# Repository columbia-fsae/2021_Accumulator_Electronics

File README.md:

View this project on [CADLAB.io](https://cadlab.io/project/23124). 

# 2021_Accumulator_Electronics

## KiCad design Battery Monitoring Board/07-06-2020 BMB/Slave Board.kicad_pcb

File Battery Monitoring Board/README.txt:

Include the following libraries from KiCAD Libraries folder:

SYMBOL LIBRARIES:

1) arduino_shieldsNCL
2) LTC6820IMS#PBF
3) LTC6804-2
4) arduino_micro_shield

FOOTPRINT LIBRARIES:

1) arduino_shields
2) Arduino
3) LTC6804-2
4) LTC6820IMS#PBF
5) Arduino_Shield_Modules_for_KiCad_V3

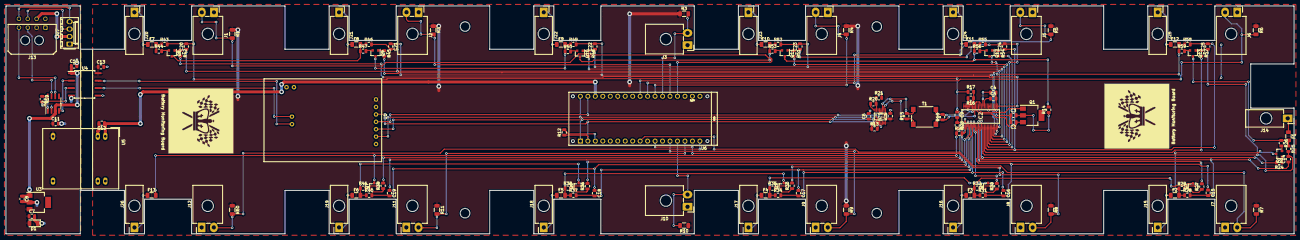
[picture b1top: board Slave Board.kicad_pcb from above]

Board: 2 copper layers, 438.0 x 77.5 mm, 148 parts (0 on the bottom side), 122 nets.

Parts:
C1, C3, C6, C7, C8, C9, C10, C11, C12, C13: 100n; C_0805_2012Metric
C2, C4, C5: 1u; C_0805_2012Metric
C14, C15, C16, C17, C18, C19, C20, C21, C22, C23, C24, C25: 10n; C_0805_2012Metric
D1: DIODE; D_1206_3216Metric
F1, F2, F3, F4, F5, F6, F7, F8, F9, F10, F11, F12, F13: Fuse; Fuse_1206_3216Metric
IC1: LTC6820IMS#PBF; SOP50P490X110-16N
IC2: LTC6804-2; SOP50P780X200-48N
J1, J2, J3, J4, J5, J6, J7, J8, J9, J10, J11, J12: Conn_01x02; TE_MATE-N-LOK_1-770966-x_1x02_P4.14mm_Horizontal
J13: Conn_01x08; Molex_Micro-Fit_3.0_43045-0800_2x04_P3.00mm_Horizontal
J14, J15, J16, J17, J18, J19, J20, J21, J22, J23, J24, J25, J26: Conn_01x01; TE_MATE-N-LOK_1-794374-x_1x01_P4.14mm_Horizontal
J27: Conn_01x04; Molex_KK-254_AE-6410-04A_1x04_P2.54mm_Vertical
Q1: Q_NPN_BCE; SOT-223
Q2, Q3, Q4, Q5, Q6, Q7, Q8, Q9, Q10, Q11, Q12, Q13: Q_PMOS_GSD; SOT-23
R1, R2, R3, R4, R5, R6, R7, R8, R9, R10, R11, R60: 680; R_1206_3216Metric
R12: NC; R_0805_2012Metric
R13: 5k; R_0805_2012Metric
R14, R15, R18, R22, R23, R25, R28, R31, R34, R37, R40, R43, R46, R49, R52, R55, R58: 100; R_0805_2012Metric
R16, R20: 1k21; R_0805_2012Metric
R17, R21: 860; R_0805_2012Metric
R19: 10k; R_0805_2012Metric
R24, R27, R30, R33, R36, R39, R42, R45, R48, R51, R54, R57: 3k3; R_0805_2012Metric
R26, R29, R32, R35, R38, R41, R44, R47, R50, R53, R56, R59: 33; R_0805_2012Metric
T1: PE-68386NL; Pulse_PA2001NL
U1: MCP2551_CANmodule; MCP2515_ArduinoShield
U2: MCP2551-I-SN; SOIC-8_3.9x4.9mm_P1.27mm
U3: OKI-78SR-3.3_1.5-W36-C; SOT-223
U4: ISO1050DUB; SOP-8_6.62x9.15mm_P2.54mm
U5: TMR_1-1212; Converter_DCDC_TRACO_POWER_TEL_10-xxxx_THT
U6: ARDUINO_MICRO_SHIELD; Arduino_Micro_Socket

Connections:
+5V: C1.1, C6.1, C13.1, IC1.1, IC1.6, IC1.7, IC1.8, IC1.9, IC1.12, R1.1, R2.1, R3.1, R4.1, R5.1, R6.1, R7.1, R8.1, R9.1, R10.1, R11.1, R13.1, R60.1, U1.7, U4.8, U6.5V
+12V: C7.1, C11.1, D1.2, J13.2, U3.3, U5.2
C0: C2.2, C3.1, C4.2, C5.2, C9.1, C20.2, IC2.26, IC2.30, IC2.31, IC2.45, IC2.46, IC2.47, IC2.48, R17.1, R43.2
C1: C20.1, C21.2, IC2.24, R46.2
C2: C21.1, C22.2, IC2.22, R49.2
C3: C22.1, C23.2, IC2.20, R52.2
C4: C23.1, C24.2, IC2.18, R55.2
C5: C24.1, C25.2, IC2.16, R58.2
C6: C14.2, C25.1, IC2.14, R25.2
C7: C14.1, C15.2, IC2.12, R28.2
C8: C15.1, C16.2, IC2.10, R31.2
C9: C16.1, C17.2, IC2.8, R34.2
C10: C17.1, C18.2, IC2.6, R37.2
C11: C18.1, C19.2, IC2.4, R40.2
C12: C19.1, IC2.2, R22.2
CANH: J13.3, U2.7
CANL: J13.4, U2.6
CS: IC1.5, R12.1, U1.5, U6.SS
Cell0: F7.2, R43.1, R44.1
Cell1: F8.2, Q8.3, R46.1, R47.1
Cell2: F9.2, Q9.3, R49.1, R50.1
Cell3: F10.2, Q10.3, R52.1, R53.1
Cell4: F11.2, Q11.3, R14.2, R55.1, R56.1
Cell5: F12.2, Q12.3, R58.1, R59.1
Cell6: F1.2, Q13.3, R25.1, R26.1
Cell7: F2.2, Q2.3, R28.1, R29.1
Cell8: F3.2, Q3.3, R31.1, R32.1
Cell9: F4.2, Q4.3, R34.1, R35.1
Cell10: F5.2, Q5.3, R37.1, R38.1
Cell11: F6.2, Q6.3, R40.1, R41.1
Cell12: F13.2, Q7.3, R22.1, R23.2
DCDC+: J13.6, J27.2
DRV: IC2.38, Q1.1
GND: C7.2, C8.2, C10.2, C11.2, D1.1, J13.1, J13.5, J27.1, R19.2, U2.2, U3.2, U4.4, U5.1
GND_ISO: C1.2, C6.2, C12.2, C13.2, IC1.13, IC1.14, J1.1, J2.1, J3.1, J4.1, J5.1, J6.1, J7.1, J8.1, J9.1, J10.1, J11.1, J12.1, R21.2, U1.6, U4.5, U5.6, U6.GND
IM: IC1.10, R15.1, T1.3
IMA: IC2.41, R18.1, T1.4
IP: IC1.11, R15.2, T1.1
IPA: IC2.42, R18.2, T1.6
ISO_CANH: U1.8, U4.7
ISO_CANL: U1.9, U4.6
unnamed: C3.2, Q1.2, R14.1
unnamed: C4.1, IC2.35
unnamed: C5.1, IC2.34
unnamed: C9.2, IC2.1, R23.1
unnamed: F1.1, J14.1
unnamed: F2.1, J15.1
unnamed: F3.1, J16.1
unnamed: F4.1, J17.1
unnamed: F5.1, J18.1
unnamed: F6.1, J19.1
unnamed: F7.1, J20.1
unnamed: F8.1, J21.1
unnamed: F9.1, J22.1
unnamed: F10.1, J23.1
unnamed: F11.1, J24.1
unnamed: F12.1, J25.1
unnamed: F13.1, J26.1
unnamed: IC1.15, R20.2, R21.1
unnamed: IC1.16, R20.1
unnamed: IC2.43, R16.1, R17.2
unnamed: IC2.44, R16.2
unnamed: Q2.1, R24.1
unnamed: Q2.2, R26.2
unnamed: Q3.1, R27.1
unnamed: Q3.2, R29.2
unnamed: Q4.1, R30.1
unnamed: Q4.2, R32.2
unnamed: Q5.1, R33.1
unnamed: Q5.2, R35.2
unnamed: Q6.1, R36.1
unnamed: Q6.2, R38.2
unnamed: Q7.1, R39.1
unnamed: Q7.2, R41.2
unnamed: Q8.1, R42.1
unnamed: Q8.2, R44.2
unnamed: Q9.1, R45.1
unnamed: Q9.2, R47.2
unnamed: Q10.1, R48.1
unnamed: Q10.2, R50.2
unnamed: Q11.1, R51.1
unnamed: Q11.2, R53.2
unnamed: Q12.1, R54.1
unnamed: Q12.2, R56.2
unnamed: Q13.1, R57.1
unnamed: Q13.2, R59.2
unnamed: R12.2, U6.TX
unnamed: R19.1, U2.8
PWM_Fans: J13.8, J27.4
RXD: U2.4, U4.2
S1: IC2.25, R42.2
S2: IC2.23, R45.2
S3: IC2.21, R48.2
S4: IC2.19, R51.2
S5: IC2.17, R54.2
S6: IC2.15, R57.2
S7: IC2.13, R24.2
S8: IC2.11, R27.2
S9: IC2.9, R30.2
S10: IC2.7, R33.2
S11: IC2.5, R36.2
S12: IC2.3, R39.2
SCK: IC1.4, U1.2, U6.SCK
SI: IC1.2, U1.3, U6.MO
SO: IC1.3, R13.2, U1.4, U6.MI
Sens_Fans: J13.7, J27.3
T0: J1.2, R1.2, U6.A0
T1: J2.2, R2.2, U6.A1
T2: J3.2, R3.2, U6.A2
T3: J4.2, R4.2, U6.A3
T4: J5.2, R5.2, U6.A4
T5: J6.2, R6.2, U6.A5
T6: J7.2, R7.2, U6.4
T7: J8.2, R8.2, U6.6
T8: J9.2, R9.2, U6.8
T9: J10.2, R10.2, U6.9
T10: J11.2, R11.2, U6.10
T11: J12.2, R60.2, U6.12
TXD: U2.1, U4.3
VCC: C8.1, C10.1, U2.3, U3.1, U4.1
VCC_ISO: C12.1, U5.4, U6.VI
Vreg: C2.1, IC2.37, IC2.40, Q1.3

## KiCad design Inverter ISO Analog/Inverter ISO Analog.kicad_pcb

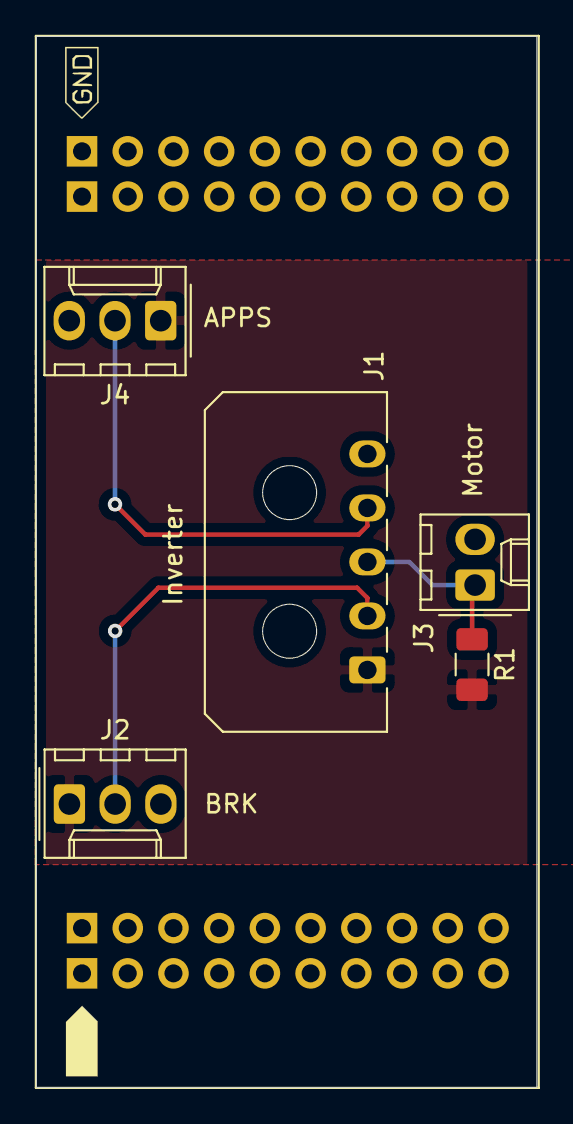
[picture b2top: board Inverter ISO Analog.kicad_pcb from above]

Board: 2 copper layers, 27.8 x 58.4 mm, 6 parts (0 on the bottom side), 5 nets.

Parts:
J1: Inverter; Molex_Micro-Fit_3.0_43650-0500_1x05_P3.00mm_Horizontal
J2: Brake Sensor; Molex_KK-254_AE-6410-03A_1x03_P2.54mm_Vertical
J3: Motor; Molex_KK-254_AE-6410-02A_1x02_P2.54mm_Vertical
J4: Accelerator Sensor; Molex_KK-254_AE-6410-03A_1x03_P2.54mm_Vertical
R1: 330k; R_1206_3216Metric
U1: C2000BoosterPack_Shield

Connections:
+5V: J1.1, J2.1, J4.1, R1.2
APPS: J1.4, J4.2
BRK: J1.2, J2.2
GNDA: J1.5, J2.3, J3.2, J4.3
Therm+: J1.3, J3.1, R1.1

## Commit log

2020-07-19 First files added
2020-07-19 Backlink to CADLAB.io has been added.
2020-07-19 First PCBs added
2020-07-19 File format changed to accept large files
2020-07-21 Accumulator Base PCB schematic added, footprints not included
2020-07-21 Update .gitattributes
    .kicad_pcb and .kicad_pcb-bak files removed in order to enable CADLAB.io visualizing
2020-07-21 Energy meter LV power connector added to Accumulator Base schematic
2020-07-21 Files re-uploaded
2020-07-29 Accumulator Base layout with no traces
2020-08-01 Blind mate connector added to BMB
2020-08-02 BMB wired BMI connector
2020-08-05 Libraries added to project folders
2020-08-05 Deleted all ignored files
2020-08-14 Changed right angle connectors to straight ones and added LCD and EM connectors
2020-08-14 BMB shortened
2020-08-16 Replaced TSMP connector
2020-08-18 Created isolated PCB for the inverter's analog signals and added 3D model to Base PCB
2020-08-21 fp-lib-table files unignored and pull-down resistors added on NMOS gates in Base PCB
2020-08-26 Base PCB finished with traces
2020-09-12 Vibration damping fasteners added to all PCB shields
